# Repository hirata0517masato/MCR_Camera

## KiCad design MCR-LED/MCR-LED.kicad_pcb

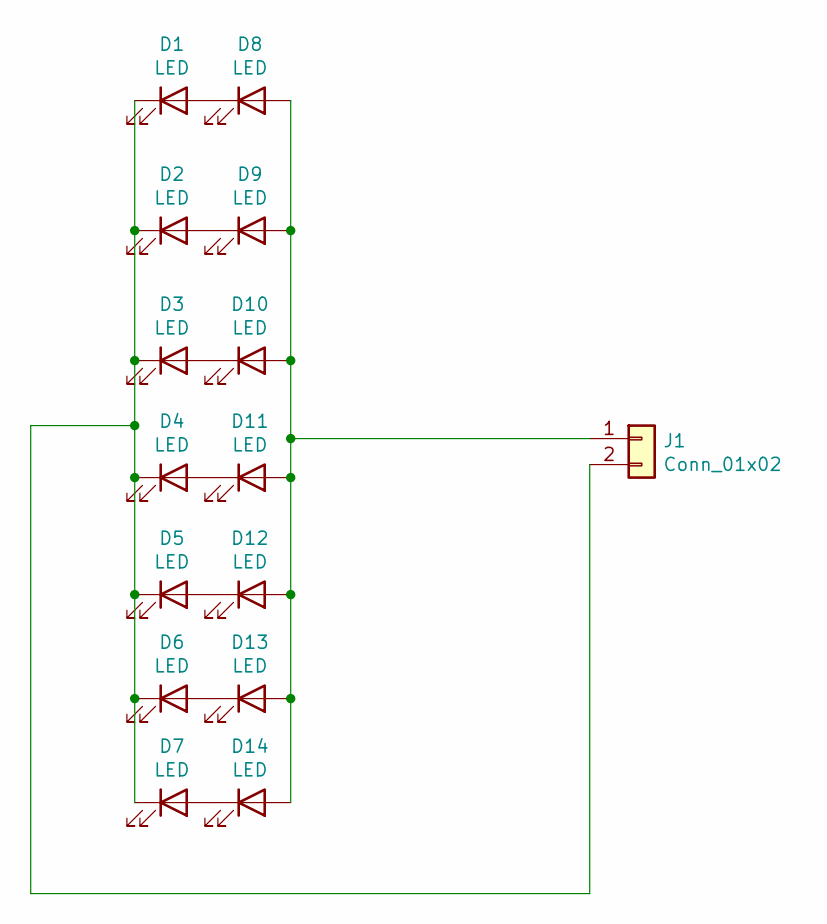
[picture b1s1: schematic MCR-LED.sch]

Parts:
D1, D2, D3, D4, D5, D6, D7, D8, D9, D10, D11, D12, D13, D14: LED; LED_D5.0mm
J1: Conn_01x02; PinHeader_1x02_P2.54mm_Vertical

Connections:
unnamed: D1.1 (K), D2.1 (K), D3.1 (K), D4.1 (K), D5.1 (K), D6.1 (K), D7.1 (K), J1.2
unnamed: D1.2 (A), D8.1 (K)
unnamed: D2.2 (A), D9.1 (K)
unnamed: D3.2 (A), D10.1 (K)
unnamed: D8.2 (A), D9.2 (A), D10.2 (A), D11.2 (A), D12.2 (A), D13.2 (A), D14.2 (A), J1.1
unnamed: D4.2 (A), D11.1 (K)
unnamed: D5.2 (A), D12.1 (K)
unnamed: D6.2 (A), D13.1 (K)
unnamed: D7.2 (A), D14.1 (K)

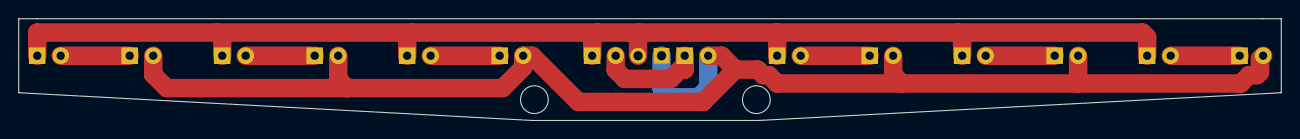
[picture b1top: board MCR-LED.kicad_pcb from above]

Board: 2 copper layers, 136.5 x 11.0 mm, 15 parts (0 on the bottom side), 9 nets.

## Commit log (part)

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2018-02-25 first
2019-01-24 2019-01-25
2019-02-10 2019-2-10
    update
2019-03-30 noV
    バッテリー電圧の監視を取りやめ
2019-04-08 camera-update
    軽微な修正
2019-07-27 update20190727
    update
2020-03-16 update2020-3-16
    update
2020-03-23 update2020-3-23
    update
2020-09-05 update2020-09-05
    update
2020-11-03 mcr-r8c38-rx
    自作基板対応
2020-12-28 2020-12-28
    2020-12-28
2022-01-08 2022-1-8
    2022-1-8
2022-08-06 usb_printf
    USBでのprintfに対応
    ただし、連続して複数の出力を行うとフリーズする（バッファが足りないかも）
2022-10-29 encoder_update
    エンコーダを２層入力に変更
2022-11-22 update
    更新
2022-12-17 update
    カーブの速度UP
2023-01-05 update
    コース記憶処理の高速化（ログ出力なし）モードを追加。トーナメント時に使用する想定。
    パラメータ調整
2023-03-19 update
    焼うどんカップでのコード
2023-07-31 debug
    クランク、ハーフ後、ほげmm以内はクランク、ハーフを無視する機能の初期値が０のため、スタート後、ほげmm以内も無視する問題を修正
2023-08-10 common
    ビルドに必要なデータが不足していたのでコミット（バックアップ目的）
2023-08-12 update
    パラメータ更新
2023-08-13 camera_debug
    急激に明るくなった際に露光量の変化量がオーバーフローしていた可能性があるため修正
    急激に明るくなった際に正常に撮影できなかった原因の可能性が高い
2023-08-14 update
    カメラ用のパラメータ調整
2023-08-20 camera_revert
    急激な明るさ変化対策版は真っ白、真っ黒判定がいまいちだったので元に戻す。
    コ
    ※急激に明るくなった際に露光時間がオーバーフローするバグも元に戻った
2023-08-20 bugfix_and_update
    ・坂検出用ジャイロの値が数ms減少（坂判定）した場合、坂開始直後に終了判定が行われるバグを修正
    ・クランクショートカット時にショートカットできる距離だが減速が間に合わない場合のモードを追加
2023-09-03 LED
    LED基板のデータを作成
2023-11-05 camera_update
    ゲートスタート時、ゲートバーや周辺の明るさに露光量が調整され、スタート直後に真っ暗になる問題を軽減
2023-11-05 update
    ハーフ：ポールありor無しをdefineで変更できるように設定を追加
2023-12-23 update
    パラメータ調整
    ポールありの調整
2023-12-30 update
    jmcr2024終了後
2024-01-13 update
    初回加速時にブレークモードにする
    クランク、ハーフ直後は別パラメータにする
2024-01-27 update
    調整
2024-02-03 update
    パラメータ調整
2024-02-11 update
    坂検出後に走行用パラメータが坂用に切り替わらないバグが発生。原因解析中。
2024-02-23 not_jump
    坂ジャンプ対策
2024-03-02 DCX16S
    モータ変更によるパラメータ調整中
2024-03-16 パラメータ調整
    調整中
2024-03-24 焼きうどんカップ
    焼きうどんカップ出場時のコード
2024-03-30 update
    ギア比変更 13:53
    初速は前モータ程度
    トルクが減少したため、バタつきが軽減され速度が上がった
2024-05-03 camera
    ２値化の閾値を上げた。白線の幅は細くなるが黒床の一部が外乱で照らされても白と誤検知しにくくなるはず
2024-05-04 saka-test
    坂頂上付近でのジャンプを軽減するため、頂上付近では後輪出力を０にする
    （動作未確認）
2024-05-04 update
    距離計測のアルゴを更新
    滑り対策でいれていたソフトがレーンチェンジ直後の計測に悪影響があったため修正。距離計測の誤差が減少するはず（未確認）
2024-05-05 update
    カーブで角度がきつくなりすぎないように上限値を追加（外側を減速せずに走る方針）
    カーブ時のオフセットのマイナス側の式が間違っていたので修正
2024-05-05 update
    クランクショートカットで内側を曲がりすぎた場合の対策
    逆ハンが弱かったのでパラメータ調整
    大回りになるように距離を微調整
2024-05-06 update
    クランクショートカットで内側をに入りすぎたときはフラグを立て、真っ黒になるまで復帰できないように変更
2024-08-12 update
    第2回reRo杯でのプログラム
2024-08-12 update
    ２値化の閾値を変更（元に戻す）
2024-09-14 update
    ギア比変更によるパラメータ調整
    フロント13:53 リア14:52
2024-09-16 update
    急に暗くなた場合でも明るさの最大値と最小値の差分があれば２値化するように変更
2024-09-16 update
    電池を新品に交換するとモータの出力が大幅に変わったため再調整中
2024-11-04 update
    目標の明るさ最大値を下げ、撮影周期を高速化する。コース記憶の距離計測の精度UPを期待する。
2025-02-01 camera-update
    露光量の調整スピードを上げた（元に戻した）
    明るさの変化を安定させるために速度を落としていたが、照明などの急な変化に耐えられなかった。
2025-02-01 update
    クランク直後のカーブで出力を落とす設定が反映されない場合があったので修正
2025-02-09 update
    明るさ目標値を760に戻す。周期が遅くなるが安定しやすくなる。
    露光量調整、閾値調整で使用する明るさ最大値を２番目に明るい値に変更する。１番は異常値の可能性がある
2025-05-25 rename
    ・変数名の先頭に型を判別する文字を追加
    ・未使用のコードを削除
2025-05-25 MAX_TOPSPEED
    JMCR指定モータと同等の最大速度に制限するブレーキを追加
2025-06-07 update
    以下の車体変更によりパラメータの調整
    ・タイヤ幅40mm→29mm
    ・赤電池→eneloopPo
2025-07-12 update
    ショートカットの調整
    クランクの距離が短いときもショートカットするモードを追加
    クランクショートカットの直後のカーブのみパラメータを別で設定
2025-07-14 update
    坂道の終了条件にハンドル角度がまっすぐであることを追加。坂道の距離は目視で入力しているため、実際より短く設定すると不安定な状態で坂を終了することになる。かつ、通常と坂はコース記憶の直線判定の許容角度が異なるため、坂下り中に直線距離がリセットされる可能性があった
2025-08-11 update
    reRo杯に参加したときのプログラム
2025-10-20 debug
    デバッグ用にフレームレート出力機能を追加
2025-11-03 Revert "update"
    This reverts commit efe233ca053cd9c503e60f9cac4952f02e802190.
2025-11-03 Revert "debug"
    This reverts commit bcacd073ebb8b02d7088a770726f2ed6c109c7b8.
2025-11-03 camera
    動作確認済みのバージョンに戻す
    メモ：周期が遅いかも？走行は可能
2025-12-20 update
    パラメータ調整
    カメラの2Line加算のテスト
2025-12-20 update
    坂検出の閾値変更
    坂以外で誤検知していたため変更
2025-12-26 camera
    2Lineを加算して露光時間を削減する作戦は失敗。１Lineｘ２と同様のためノイズが増える。
2025-12-27 camera
    露光時間の変更速度を向上
    明るさが不安定になるが、急な明るさの変化に対応できるため採用
2025-12-29 update
    パラメータ調整
    レーンチェンジの曲がり中の設定値をもとに戻す。本当は進入と同じに設定したいが不安定のため戻す
2025-12-30 debug
    設定ミスの修正
2026-01-04 camera-fps
    目標の輝度値を下げて周期を少し向上させる
2026-02-08 update
    目標の明るさを上げた。周期は遅くなるけど誤検知が減る。
2026-02-08 koube
    パラメータ調整
2026-02-08 c_cut not auto
    クランクショートカット時の距離が短いor長いの現在速度による自動調整機能を廃止
    どちらが動作しているか不明となるので、調整が困難になる
2026-02-09 camera
    ・幅が太いときはクランクの可能性があるので、最小値が低くなければ真っ白にする処理を追加
    ・目標の明るさを下げ、制御周期を上げる
2026-02-09 update
    コース記憶かつクランクは通常モードでのクランク距離ショートorロング判定を追加
2026-02-11 start_wait
    スタート時に走行開始を遅らせる処理を実装
    ディップスイッチでキャンセル可能
2026-02-11 update
    ・直線コース記憶を1000mm未満無視から500mm未満無視に変更
    ・クランクショートカットの復帰条件の変更
2026-02-28 camera
    カメラの安定板ソフト
2026-03-07 data_f_make
    ログ出力時のコース形状記憶機能の改善
    坂道終了直後はブレる可能性があるので、カーブ判定を坂用を使用するように変更。
    走行中は上記の仕様だったが、コース形状記憶は対応していなかった。
2026-03-08 update
    記憶した直線の通過判定の変更
    現在の走行距離が短いときは通過判定しないように変更
2026-03-18 camera
    全白検出率を上げるための調整
2026-03-18 update
    パラメータ調整
    直線速度を通常とコース記憶で別に設定できるように変更
2026-03-22 焼うどん2026
    焼うどん2026のコード
